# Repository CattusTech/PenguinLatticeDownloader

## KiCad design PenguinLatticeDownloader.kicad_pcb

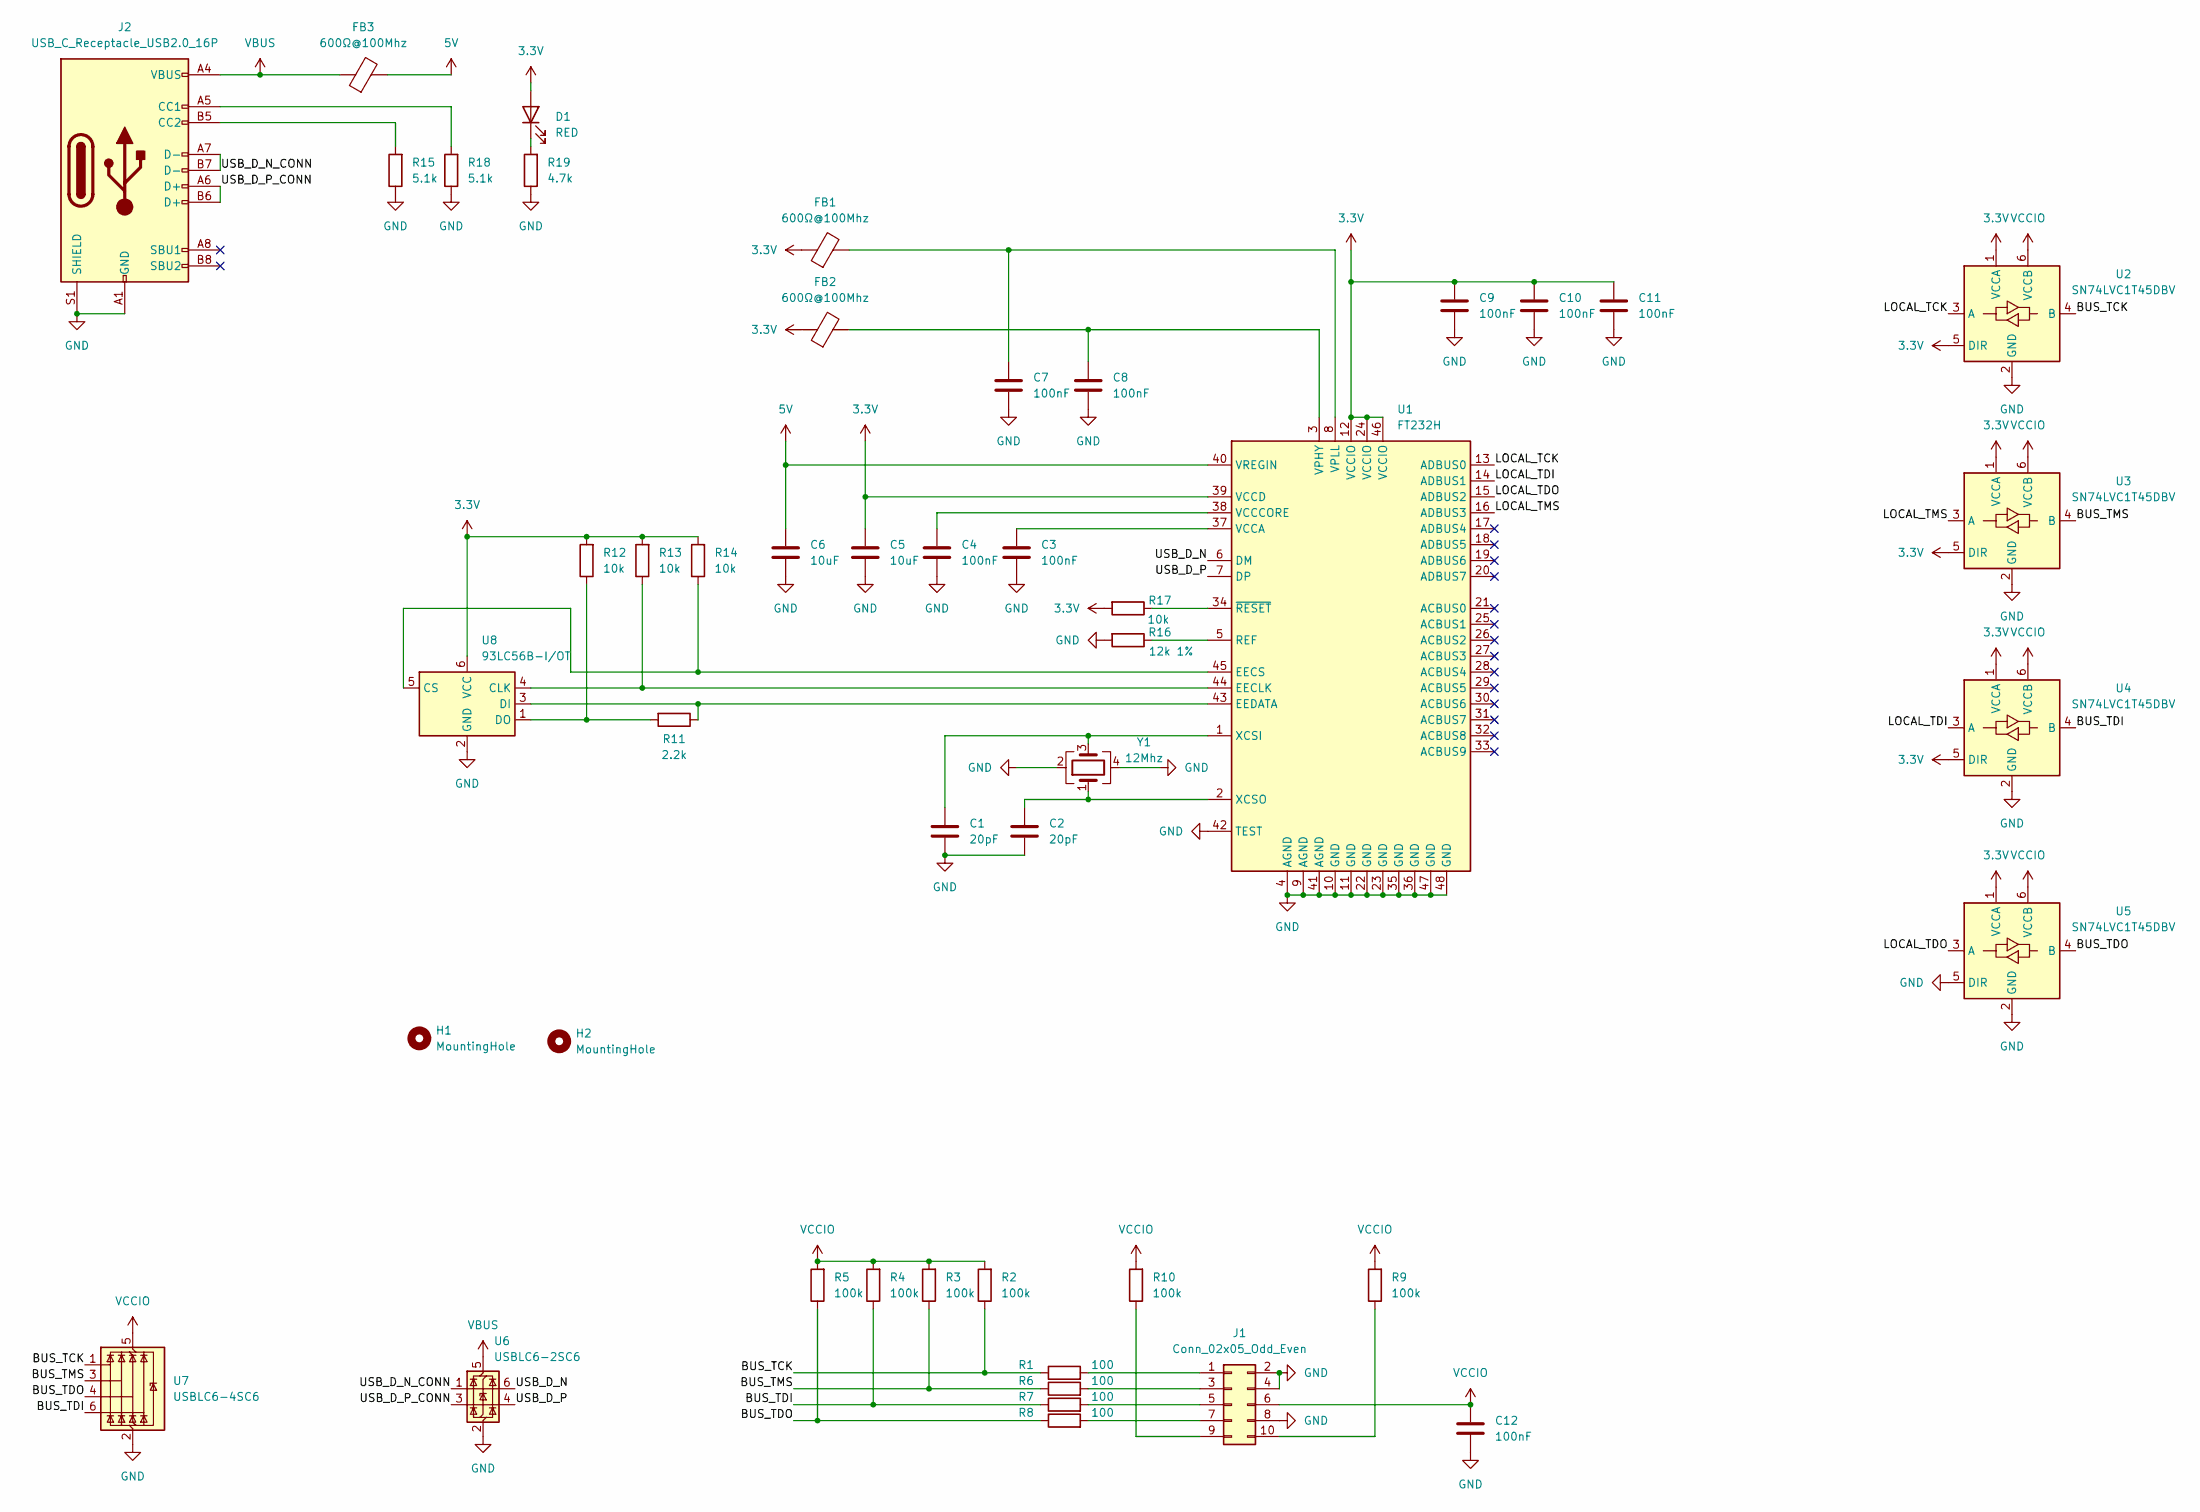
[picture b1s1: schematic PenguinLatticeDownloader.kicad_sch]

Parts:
C1, C2: 20pF; C_0603_1608Metric
C3, C4, C7, C8, C9, C10, C11, C12: 100nF; C_0603_1608Metric
C5, C6: 10uF; C_0603_1608Metric
D1: RED; LED_0603_1608Metric
FB1, FB2: 600Ω@100Mhz; L_0603_1608Metric
FB3: 600Ω@100Mhz; L_0805_2012Metric
H1, H2: MountingHole; MountingHole_2.2mm_M2_ISO14580
J1: Conn_02x05_Odd_Even; IDC-Header_2x05_P2.54mm_Vertical
J2: USB_C_Receptacle_USB2.0_16P; USB_C_Receptacle_GCT_USB4105-xx-A_16P_TopMnt_Horizontal
R1, R6, R7, R8: 100; R_0603_1608Metric
R2, R3, R4, R5, R9, R10: 100k; R_0603_1608Metric
R11: 2.2k; R_0603_1608Metric
R12, R13, R14, R17: 10k; R_0603_1608Metric
R15, R18: 5.1k; R_0603_1608Metric
R16: 12k 1%; R_0603_1608Metric
R19: 4.7k; R_0603_1608Metric
U1: FT232H; LQFP-48_7x7mm_P0.5mm
U2, U3, U4, U5: SN74LVC1T45DBV; SOT-23-6
U6: USBLC6-2SC6; SOT-23-6
U7: USBLC6-4SC6; SOT-23-6
U8: 93LC56B-I/OT; SOT-23-6
Y1: 12Mhz; Crystal_SMD_3225-4Pin_3.2x2.5mm

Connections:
3.3V: C5.2, C9.2, C10.2, C11.2, D1.2 (A), FB1.1, FB2.1, R12.2, R13.2, R14.2, R17.2, U1.12 (VCCIO), U1.24 (VCCIO), U1.39 (VCCD), U1.46 (VCCIO), U2.1 (VCCA), U2.5 (DIR), U3.1 (VCCA), U3.5 (DIR), U4.1 (VCCA), U4.5 (DIR), U5.1 (VCCA), U8.6 (VCC)
5V: C6.2, FB3.2, U1.40 (VREGIN)
/BUS_TCK: R1.1, R2.1, U2.4 (B), U7.1 (I/O1)
/BUS_TDI: R4.1, R7.1, U4.4 (B), U7.6 (I/O4)
/BUS_TDO: R5.1, R8.1, U5.4 (B), U7.4 (I/O3)
/BUS_TMS: R3.1, R6.1, U3.4 (B), U7.3 (I/O2)
/LOCAL_TCK: U1.13 (ADBUS0), U2.3 (A)
/LOCAL_TDI: U1.14 (ADBUS1), U4.3 (A)
/LOCAL_TDO: U1.15 (ADBUS2), U5.3 (A)
/LOCAL_TMS: U1.16 (ADBUS3), U3.3 (A)
/USB_D_N: U1.6 (DM), U6.6 (I/O1)
/USB_D_N_CONN: J2.A7 (D-), J2.B7 (D-), U6.1 (I/O1)
/USB_D_P: U1.7 (DP), U6.4 (I/O2)
/USB_D_P_CONN: J2.A6 (D+), J2.B6 (D+), U6.3 (I/O2)
GND: C1.1, C2.1, C3.1, C4.1, C5.1, C6.1, C7.1, C8.1, C9.1, C10.1, C11.1, C12.1, J1.2, J1.4, J1.8, J2.A1 (GND), J2.A12 (GND), J2.B1 (GND), J2.B12 (GND), J2.S1 (SHIELD), R15.1, R16.2, R18.1, R19.1, U1.4 (AGND), U1.9 (AGND), U1.10 (GND), U1.11 (GND), U1.22 (GND), U1.23 (GND), U1.35 (GND), U1.36 (GND), U1.41 (AGND), U1.42 (TEST), U1.47 (GND), U1.48 (GND), U2.2 (GND), U3.2 (GND), U4.2 (GND), U5.2 (GND), U5.5 (DIR), U6.2 (GND), U7.2 (GND), U8.2 (GND), Y1.2, Y1.4
unnamed: D1.1 (K), R19.2
unnamed: J1.1, R1.2
unnamed: J1.3, R6.2
unnamed: J1.5, R7.2
unnamed: J1.7, R8.2
unnamed: J1.9, R10.1
unnamed: J1.10, R9.1
unnamed: J2.A5 (CC1), R18.2
unnamed: J2.B5 (CC2), R15.2
unnamed: R13.1, U1.44 (EECLK), U8.4 (CLK)
unnamed: R14.1, U1.45 (EECS), U8.5 (CS)
unnamed: R11.1, U1.43 (EEDATA), U8.3 (DI)
unnamed: R16.1, U1.5 (REF)
unnamed: C3.2, U1.37 (VCCA)
unnamed: C4.2, U1.38 (VCCCORE)
unnamed: C8.2, FB2.2, U1.3 (VPHY)
unnamed: C7.2, FB1.2, U1.8 (VPLL)
unnamed: C1.2, U1.1 (XCSI), Y1.3
unnamed: C2.2, U1.2 (XCSO), Y1.1
unnamed: R17.1, U1.34 (~RESET)
unnamed: R11.2, R12.1, U8.1 (DO)
VBUS: FB3.1, J2.A4 (VBUS), J2.A9 (VBUS), J2.B4 (VBUS), J2.B9 (VBUS), U6.5 (VBUS)
VCCIO: C12.2, J1.6, R2.2, R3.2, R4.2, R5.2, R9.2, R10.2, U2.6 (VCCB), U3.6 (VCCB), U4.6 (VCCB), U5.6 (VCCB), U7.5 (VBUS)

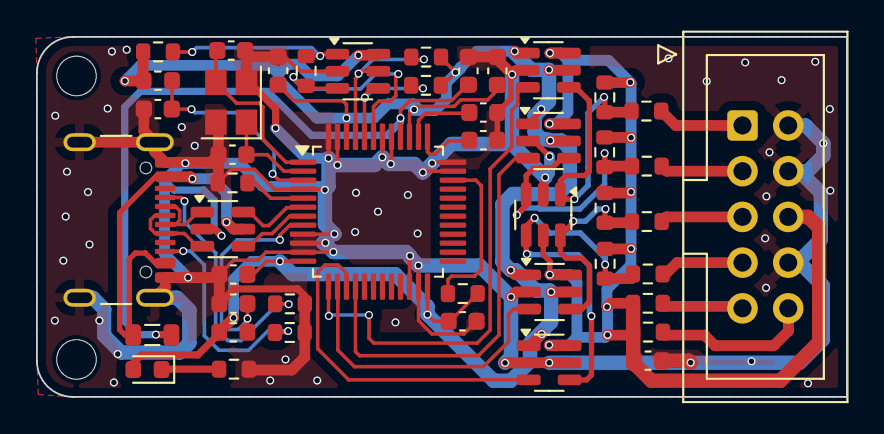
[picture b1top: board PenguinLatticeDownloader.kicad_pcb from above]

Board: 2 copper layers, 45.0 x 20.0 mm, 48 parts (0 on the bottom side), 38 nets.
